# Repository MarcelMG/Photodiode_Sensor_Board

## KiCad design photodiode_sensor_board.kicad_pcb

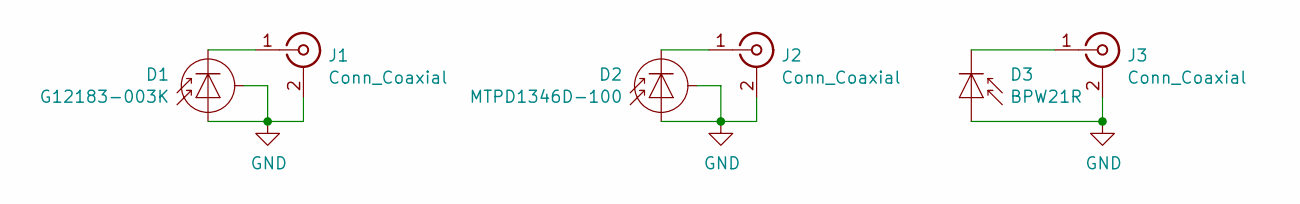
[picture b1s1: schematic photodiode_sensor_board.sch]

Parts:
D1: G12183-003K; TO-18-3_Window
D2: MTPD1346D-100; TO-46-3_Window
D3: BPW21R; TO-5-2_Window
J1, J2, J3: Conn_Coaxial; SMA_Amphenol_132291-12_Vertical

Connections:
GND: D1.2 (CASE), D1.3 (ANODE), D2.2 (ANODE), D2.3 (CASE), D3.1 (ANODE), J1.2 (Ext), J2.2 (Ext), J3.2 (Ext)
unnamed: D1.1 (KATHODE), J1.1 (In)
unnamed: D2.1 (KATHODE), J2.1 (In)
unnamed: D3.2 (KATHODE_CASE), J3.1 (In)

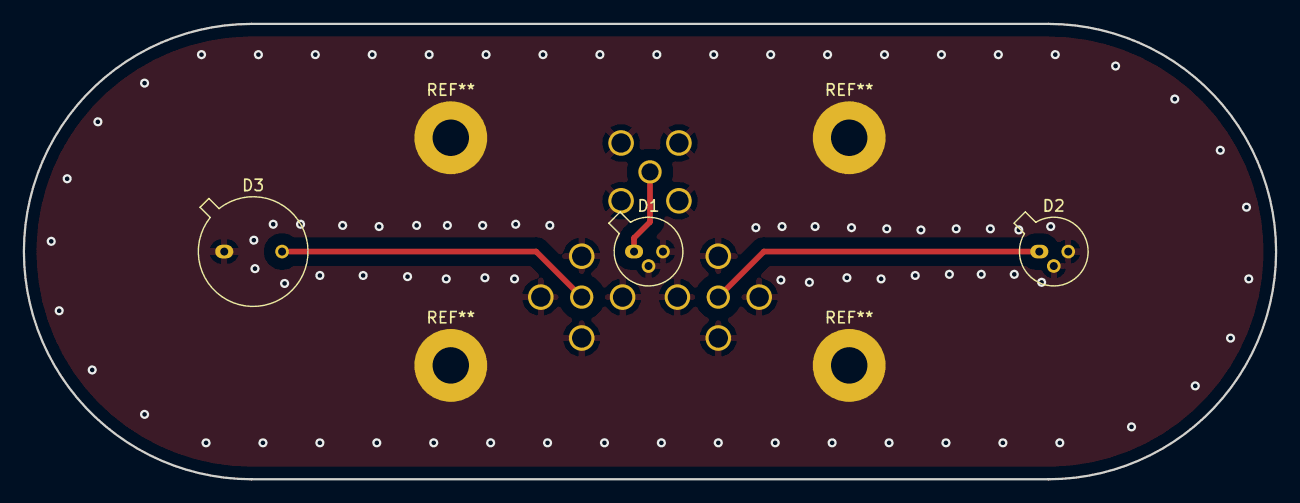
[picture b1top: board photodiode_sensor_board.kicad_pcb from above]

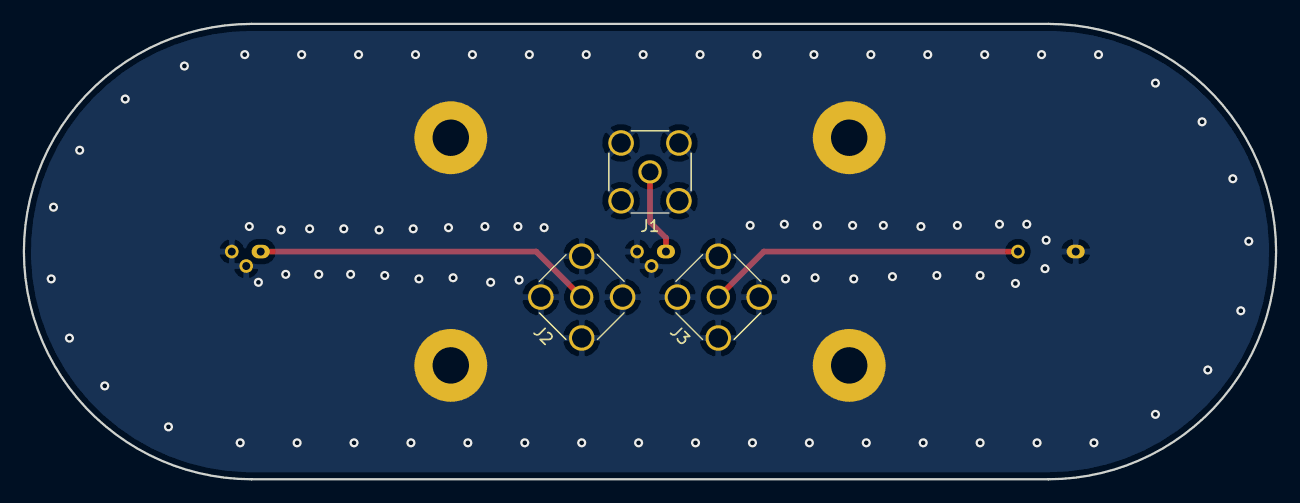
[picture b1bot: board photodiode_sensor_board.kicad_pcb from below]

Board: 2 copper layers, 110.0 x 40.0 mm, 6 parts (3 on the bottom side), 4 nets.

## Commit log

2019-12-28 fixed "oberes_teil"
2020-01-27 reorganize directories, update files
2020-01-27 added lid for closing cable slot
2020-01-28 initial upload
2020-01-30 Rename halterung.stl to halterung_35grad_neigung.stl
2020-01-30 Rename halterung_35grad_neigung.stl to halterung_v0_35grad_neigung.stl
